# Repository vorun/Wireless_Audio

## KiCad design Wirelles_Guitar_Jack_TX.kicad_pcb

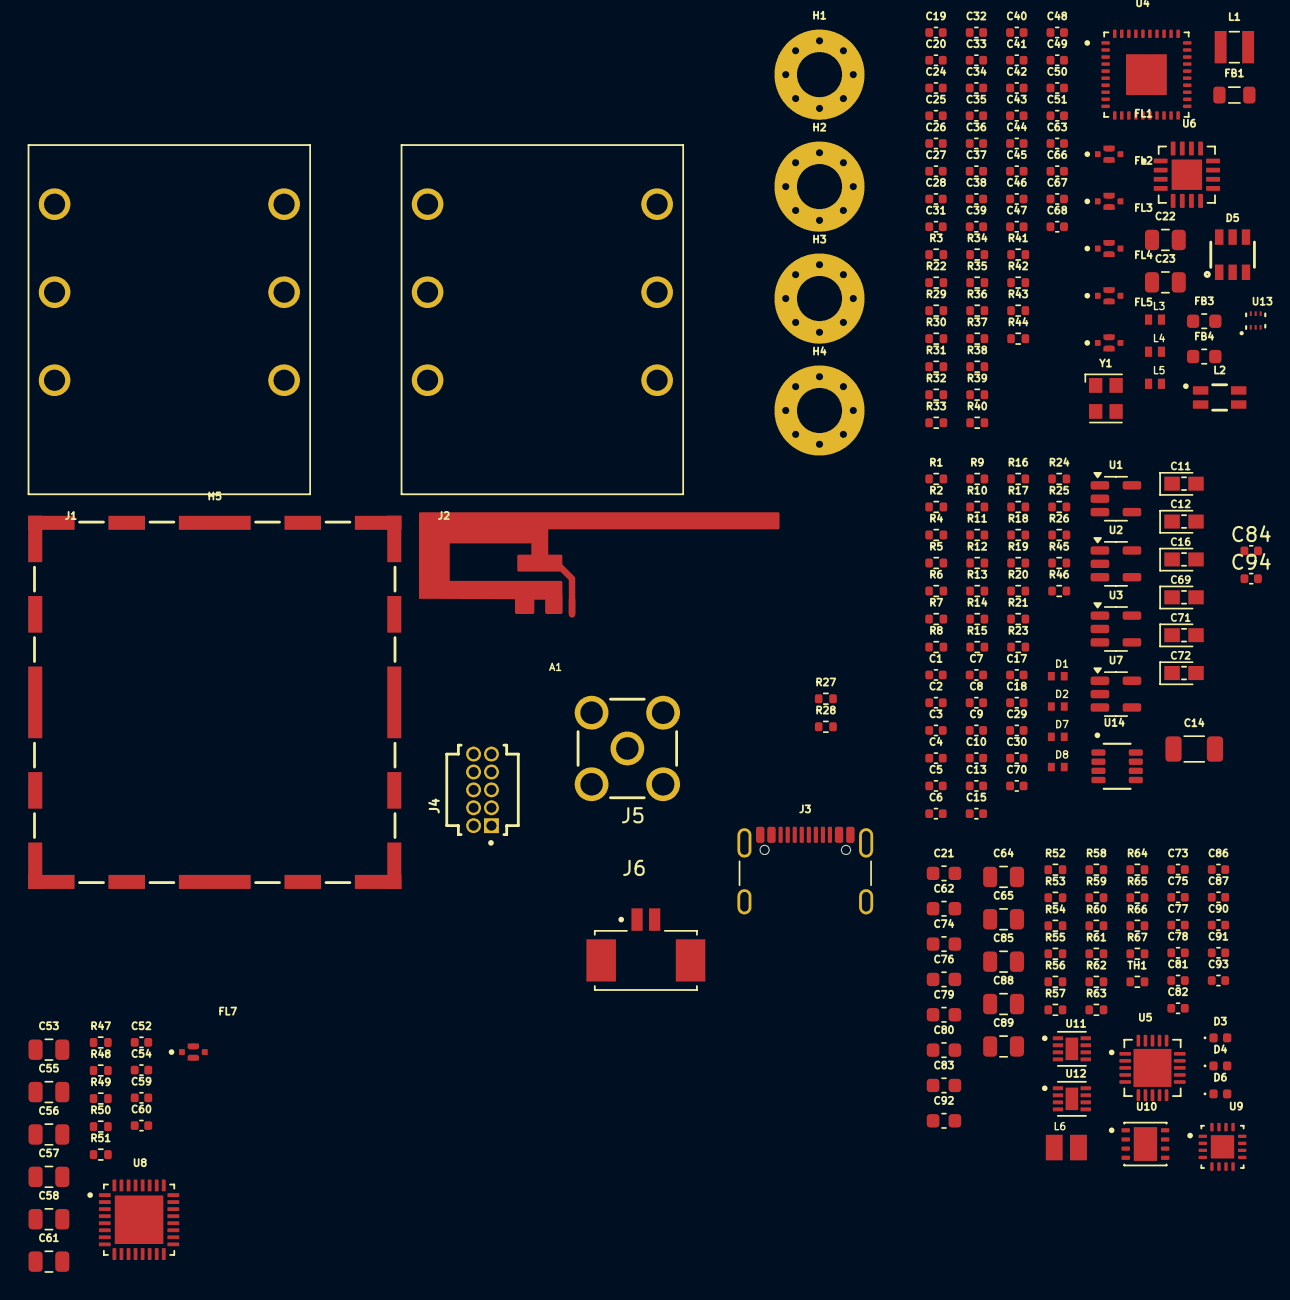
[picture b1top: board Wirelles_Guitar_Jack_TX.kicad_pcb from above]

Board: 2 copper layers, 212 parts (0 on the bottom side), 116 nets, no tracks yet.

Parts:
A1: Inverted_F_Antenna
C1, C6: 10n; C_0402_1005Metric
C2, C7, C8, C13, C18, C28, C29, C31, C37, C41, C42, C43, C44, C46, C47, C48, C49, C50, C51, C75, C77, C81, C86, C87, C90: 0.1u; C_0402_1005Metric
C3, C5: 100p; C_0402_1005Metric
C4, C17: 2n; C_0402_1005Metric
C9: 100n; C_0402_1005Metric
C10, C30: 4700p; C_0402_1005Metric
C11, C12, C16, C69, C71, C72: 2.2u; CAPC1608X90
C14: 100u; C_1206_3216Metric
C15, C63, C66, C67, C68, C70, C84, C94: C_0402_1005Metric
C19, C20: 47p; C_0402_1005Metric
C21, C62, C74, C76, C79, C80, C83: 4.7u; C_0603_1608Metric
C22, C23, C53, C55, C56, C57, C58, C61, C64, C65, C85, C88, C89: 10u; C_0805_2012Metric
C24, C32, C34, C36, C54: 1n; C_0402_1005Metric
C25: 1.2p; C_0402_1005Metric
C26: 6.8p; C_0402_1005Metric
C27: 1.8p; C_0402_1005Metric
C33, C35: 18p; C_0402_1005Metric
C38, C39, C40, C45, C59: 2.2u; C_0402_1005Metric
C52, C60, C73, C78, C82, C91: 1u; C_0402_1005Metric
C92: 1.5u; C_0603_1608Metric
C93: 1.8n; C_0402_1005Metric
D1, D2, D7, D8: 0402ESD-BI; RESC1005X35N
D3, D4, D6: LED; LED_0402_1005Metric
D5: WE-TVS-HS_SOT23-6L_824015; WE-TVS_SOT23-6L
FB1: 74279220181; L_0805_2012Metric
FB3, FB4: BLM18AG221SN1D; L_0603_1608Metric
FL1, FL2, FL3, FL4, FL5, FL7: NFM18PS105D0J3D; FIL_NFM18PS105D0J3D
H1, H2, H3, H4: MountingHole_Pad; MountingHole_3.2mm_M3_Pad_Via
H5: WE-SHC_SMD-FRAME; WE-SHC_SMD-FRAME_36103255S
J1, J2: ACJS-IH; AMPHENOL_ACJMIH
J3: USB_C_Receptacle_USB2.0_16P; USB_C_Receptacle_GCT_USB4105-xx-A_16P_TopMnt_Horizontal
J4: Conn_02x05_Odd_Even; SAMTEC_FTSH-105-01-F-D-K
J5: Conn_Coaxial; SAMTEC_SMA-J-P-X-RA-TH1
J6: 0532610271; MOLEX_0532610271
L1: 74438323012; L_Wuerth_MAPI-2512
L2: WE-CNSW_1206
L3: LQW15AN1N5B00D; INDC1006X60N
L4: LQW15AN2N2C1ZD; INDC1006X60N
L5: LQW15AN3N9C00D; INDC1006X60N
L6: 74479276168; INDC2016X100N
R1, R5: 100R; R_0402_1005Metric
R2, R4, R7, R8, R10, R45: 1M; R_0402_1005Metric
R3, R22: 2.2k; R_0402_1005Metric
R6, R9, R13, R20, R21, R46, R53, R54, R55, R62: 1k; R_0402_1005Metric
R11, R12, R18, R19, R23, R24, R25, R26: 0R; R_0402_1005Metric
R14, R17: 100; R_0402_1005Metric
R15, R16: 100k; R_0402_1005Metric
R27, R28: 5.1k; R_0402_1005Metric
R29: 1.5k; R_0402_1005Metric
R30, R31, R32, R33, R34, R47, R48, R49, R50, R51: 33R; R_0402_1005Metric
R35, R36, R37, R41, R42, R43, R52, R56, R57, R58, R59, R60, R61, R63: 10k; R_0402_1005Metric
R38, R39: R_0402_1005Metric
R40: 4.3k; R_0402_1005Metric
R44: 56k; R_0402_1005Metric
R64: 475k; R_0402_1005Metric
R65: 80.6k; R_0402_1005Metric
R66: 56.2k; R_0402_1005Metric
R67: 18.2k; R_0402_1005Metric
TH1: TMP6131DECR; R_0402_1005Metric
U1, U2, U3, U7: OPA1655DBV; SOT-23-5
U4: CC8521RAHR; QFN50P600X600X100-41N
U5: MCP73871-2CCI_ML; QFN50P400X400X100-21N
U6: CC2590RGVT; QFN65P400X400X100-17N
U8: TLV320AIC3204IRHBR; QFN50P500X500X100-33N
U9: TPS61379QWRTERQ1; VREG_TPS61379QWRTERQ1
U10: TPS7A2150; SON65P300X300X100-9N
U11, U12: TPS7A2133; SON50P200X200X80-9N
U13: SKY13351-378LF; QFN6-LF
U14: TLV9162; SOT23_DDF_TEX
Y1: ECS-2520MV-480-DN-TR; Oscillator_SMD_Kyocera_KC2520Z-4Pin_2.5x2.0mm

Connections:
+3V3A: C21.1, C73.1, FB3.1, FB4.1, U11.1 (OUT), U11.2 (OUT)
+3V3D: C59.1, C78.1, C79.1, FL2.1, FL3.1, FL5.1, FL7.1, R3.2, R22.2, U8.6 (IOVDD), U8.30 (LDO_SELECT), U12.1 (OUT), U12.2 (OUT)
+5V5: C74.1, C75.1, C76.1, C77.1, C80.1, C81.1, C86.1, C88.1, C89.1, R64.1, U9.9 (VO), U10.5 (EN), U10.8 (IN), U11.5 (EN), U11.7 (IN), U11.8 (IN), U12.5 (EN), U12.7 (IN), U12.8 (IN)
+5VA: C2.1, C7.1, C9.1, C13.1, C18.1, C82.1, C83.1, R20.2, U1.5 (V+), U2.5 (V+), U3.5 (V+), U7.5 (V+), U10.1 (OUT), U14.8 (V+)
+VBAT: C62.1, J6.1, U5.14 (VBAT), U5.15 (VBAT), U5.16 (VBAT_SENSE)
+VBL_2V5: C72.2, R8.1, R24.1, R45.1, U14.6 (-), U14.7
+VBR_2V5: C71.2, R2.1, R10.1, R25.1, U14.1, U14.2 (-)
+VBUS: D5.5, FB1.1, J3.A4 (VBUS), J3.A9 (VBUS), J3.B4 (VBUS), J3.B9 (VBUS)
+VBUSF: C23.1, C65.1, D4.2 (A), D6.2 (A), L1.2, R52.1, R57.1, R59.1, U5.2 (VPCC), U5.18 (IN), U5.19 (IN)
+VSYS(3V2-5V): C64.1, C85.1, C87.1, L6.2, U5.1 (OUT), U5.20 (OUT), U9.1 (VIN), U9.5 (MODE/SYNC), U9.15 (EN)
/ANALOG/AUDIO_IN_L: J1.T, R5.1
/ANALOG/AUDIO_IN_L_CODEC: C69.2, U8.13 (IN1_L)
/ANALOG/AUDIO_IN_R: J1.R, R1.1
/ANALOG/AUDIO_IN_R_CODEC: C16.2, U8.14 (IN1_R)
/ANALOG/AUDIO_OUT_L: C12.2, D8.2, J2.T, R16.1
/ANALOG/AUDIO_OUT_L_CODEC: R46.2, U8.22 (LOL)
/ANALOG/AUDIO_OUT_R: C11.2, D7.2, J2.R, R15.1
/ANALOG/AUDIO_OUT_R_CODEC: R13.2, U8.23 (LOR)
/ANT_PCB: A1.1 (ANT_IN), U13.1
/ANT_SMA: J5.1 (In), U13.3
/CODEC/BCLK_R: R48.2, U8.2 (BCLK)
/CODEC/DIN_R: R51.2, U8.5 (DOUT/MFP2)
/CODEC/DOUT_R: R50.2, U8.4 (DIN/MFP1)
/CODEC/MCLK_R: R47.2, U8.1 (MCLK)
/CODEC/TLV_RESET_N: C54.1, U4.8 (GIO2), U8.31 (~RESET)
/CODEC/WRCK_R: R49.2, U8.3 (WCLK)
/POWER/PG: R53.1, U5.6 (~PG)
/POWER/STAT1: R55.1, U5.8 (STAT1/*LBO)
/POWER/STAT2: R54.1, U5.7 (STAT2)
/RESET_N: C24.1, R36.1, U4.11 (RSTN)
/RF SOC/AD2: R29.1, U4.19 (AD2/GIO9)
/RF SOC/ANT_CTRL1: C68.1, R35.2, R39.1, U13.6 (VC1)
/RF SOC/ANT_CTRL2: C63.1, R37.1, R38.1, U13.4 (VC2)
/RF SOC/ANT_IN: C26.2, L3.1, U13.5 (IN)
/RF SOC/GIO12: C66.1, R38.2, U4.34 (GIO12)
/RF SOC/GIO13: C67.1, R39.2, U4.35 (GIO13)
/RF SOC/RF+: U4.24 (RF_P), U6.4 (RF_P)
/RF SOC/RF-: U4.25 (RF_N), U6.2 (RF_N)
/RF SOC/SCL: R22.1, U4.32 (SCL/GIO10)
/RF SOC/SDA: R3.1, U4.33 (SDA/GIO11)
/RF SOC/USB_D_CMC+: L2.2, R29.2, R31.1
/RF SOC/USB_D_CMC-: L2.3, R30.1
/RF SOC/USB_D_CMC_R+: C20.1, R31.2, U4.2 (USBP)
/RF SOC/USB_D_CMC_R-: C19.1, R30.2, U4.1 (USBN)
/RF SOC/xLNAEN: R33.1, U4.38 (xLNAEN/GIO15)
/RF SOC/xLNAEN_R: R33.2, U6.6 (EN)
/RF SOC/xPAEN: R34.1, R43.2, U4.36 (xPAEN/GIO14)
/RF SOC/xPAEN_R: R34.2, U6.5 (PAEN)
/USB_D+: D5.3, D5.4, J3.A6 (D+), J3.B6 (D+), L2.1
/USB_D-: D5.1, D5.6, J3.A7 (D-), J3.B7 (D-), L2.4
AVDD_TLV: C58.1, C60.1, U8.24 (AVDD)
DVDD_TLV: C55.1, C56.1, U8.29 (DVDD)
GND: A1.2 (GND), A1.3 (GND), C2.2, C3.1, C4.1, C5.1, C7.2, C9.2, C10.2, C13.2, C14.1, C17.1, C18.2, C19.2, C20.2, C21.2, C22.2, C23.2, C24.2, C25.2, C27.1, C28.2, C30.2, C31.2, C32.2, C33.2, C34.2, C35.2, C36.2, C37.2, C38.2, C39.2, C40.2, C41.2, C42.2, C43.2, C44.2, C45.2, C46.2, C47.2, C48.2, C49.2, C50.2, C51.2, C52.2, C53.2, C54.2, C55.2, C56.2, C57.2, C58.2, C59.2, C60.2, C61.2, C62.2, C63.2, C64.2, C65.2, C66.2, C67.2, C68.2, C73.2, C74.2, C75.2, C76.2, C77.2, C78.2, C79.2, C80.2, C81.2, C82.2, C83.2, C85.2, C86.2, C87.2, C88.2, C89.2, C91.2, C92.2, C93.2, D1.1, D2.1, D5.2, D7.1, D8.1, FL1.2, FL1.2_1, FL2.2, FL2.2_1, FL3.2, FL3.2_1, FL4.2, FL4.2_1, FL5.2, FL5.2_1, FL7.2, FL7.2_1, H1.1, H2.1, H3.1, H4.1, H5.1, J1.RN, J1.S, J1.SN, J1.TN, J2.RN, J2.S, J2.SN, J2.TN, J3.A1 (GND), J3.A12 (GND), J3.B1 (GND), J3.B12 (GND), J3.S1 (SHIELD), J5.2 (Ext), J6.2, J6.S1 (SHIELD), J6.S2 (SHIELD__1), L3.2, R4.2, R7.2, R15.2, R16.2, R21.1, R27.2, R28.2, R40.2, R42.1, R43.1, R44.1, R56.2, R58.2, R60.2, R61.2, R62.2, R65.2, R67.2, TH1.2, U1.2 (V-), U2.2 (V-), U3.2 (V-), U4.41 (GND), U5.10 (GND), U5.11 (GND), U5.21 (EP), U6.8 (GND), U6.9 (GND), U6.12 (GND), U6.14 (GND), U6.17 (GND), U7.2 (V-), U8.7 (IOVSS), U8.12 (SPI_SELECT), U8.17 (AVSS), U8.28 (DVSS), U8.33 (EP), U9.7 (GND), U9.8 (GND), U9.17 (EXP), U10.4 (GND), U10.9 (EP), U11.4 (GND), U11.9 (EP), U12.4 (GND), U12.9 (EP), U13.2 (GND), U14.4 (V-), Y1.2 (GND)
IOVDD: C41.1, C42.1, C43.1, C44.1, FL2.3, R35.1, R36.2, R37.2, U4.10 (IOVDD), U4.12 (IOVDD), U4.18 (IOVDD), U4.37 (IOVDD)
unnamed: C1.1, C3.2, D1.2, R1.2, R4.1
unnamed: C5.2, C6.1, D2.2, R5.2, R7.1
unnamed: C8.1, C10.1, R13.1
unnamed: C11.1, R14.1
unnamed: C12.1, R17.1
unnamed: C15.2, R12.2, R14.2, U2.1
unnamed: C4.2, C16.1, R6.2
unnamed: C17.2, C69.1, R9.2
unnamed: C22.1, FB1.2, L1.1
unnamed: C25.1, L4.2, L5.1
unnamed: C26.1, C27.2, L5.2
unnamed: C29.1, C30.1, R46.1
unnamed: C38.1, FB3.2, FL1.1
unnamed: C45.1, FB4.2, FL4.1
unnamed: C46.1, C47.1, C48.1, C49.1, C50.1, C51.1, FL4.3, U4.20 (AVDD), U4.23 (AVDD), U4.26 (AVDD), U4.27 (AVDD), U4.28 (AVDD), U4.31 (AVDD)
unnamed: C70.2, R17.2, R18.2, U7.1
unnamed: C71.1, R11.1
unnamed: C72.1, R19.1
unnamed: C84.1, R9.1, R23.2, U3.1
unnamed: C90.1, L6.1, U9.3 (SW), U9.4 (SW)
unnamed: C93.1, R66.2
unnamed: C94.1, R6.1, R26.2, U1.1
unnamed: D3.1 (K), R55.2
unnamed: D4.1 (K), R54.2
unnamed: D6.1 (K), R53.2
unnamed: J3.A5 (CC1), R28.1
unnamed: J3.B5 (CC2), R27.1
unnamed: C1.2, R2.2, U1.3 (+)
unnamed: C94.2, R25.2, R26.1, U1.4 (-)
unnamed: C8.2, R10.2, U2.3 (+)
unnamed: C15.1, R11.2, R12.1, U2.4 (-)
unnamed: C6.2, R8.2, U3.3 (+)
unnamed: C84.2, R23.1, R24.2, U3.4 (-)
unnamed: R44.2, U4.30 (RBIAS)
unnamed: R32.1, U4.21 (X1)
unnamed: C31.1, C39.1, U4.39 (DCPL)
unnamed: C40.1, FL3.3, U4.40 (DVDD)
unnamed: R59.2, U5.17 (CE)
unnamed: R62.1, U5.13 (PROG1)
unnamed: R61.1, U5.4 (PROG2)
unnamed: R60.1, U5.12 (PROG3)
unnamed: R52.2, R56.1, U5.3 (SEL)
unnamed: TH1.1, U5.5 (THERM)
unnamed: R57.2, R58.1, U5.9 (~TE)
unnamed: L4.1, U6.11 (ANT)
unnamed: R41.1, R42.2, U6.7 (HGM)
unnamed: C32.1, C33.1, C34.1, C35.1, C36.1, C37.1, FL1.3, U6.10 (AVDD_PA2), U6.13 (AVDD_LNA), U6.16 (AVDD_BIAS)
unnamed: R40.1, U6.15 (BIAS)
unnamed: C29.2, R45.2, U7.3 (+)
unnamed: C70.1, R18.1, R19.2, U7.4 (-)
unnamed: C57.1, C61.1, FL7.3, U8.26 (LDOIN/HPVDD)
unnamed: C52.1, C53.1, U8.18 (REF)
unnamed: C90.2, U9.2 (BST)
unnamed: R66.1, U9.14 (COMP)
unnamed: R64.2, R65.1, U9.13 (FB)
unnamed: R67.1, U9.16 (FREQ)
unnamed: C92.1, U9.10 (OUT)
unnamed: R63.2, U9.11 (PG)
unnamed: C91.1, R63.1, U9.6 (VCC)
unnamed: C14.2, R20.1, R21.2, U14.3 (+), U14.5 (+)
unnamed: R32.2, Y1.3 (OUTPUT)
unnamed: C28.1, FL5.3, Y1.1 (TRI_STATE), Y1.4 (VDD)

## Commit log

2025-05-07 initial_commit
2025-05-07 schematic_pdf_added
2025-05-07 sch_pdf_added
